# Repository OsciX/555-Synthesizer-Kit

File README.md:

These works were designed by Ryan Davis in 2015, and are licensed under a Creative Commons Attribution-ShareAlike 4.0 International License, which can be found 
at http://creativecommons.org/licenses/by-sa/4.0/ .

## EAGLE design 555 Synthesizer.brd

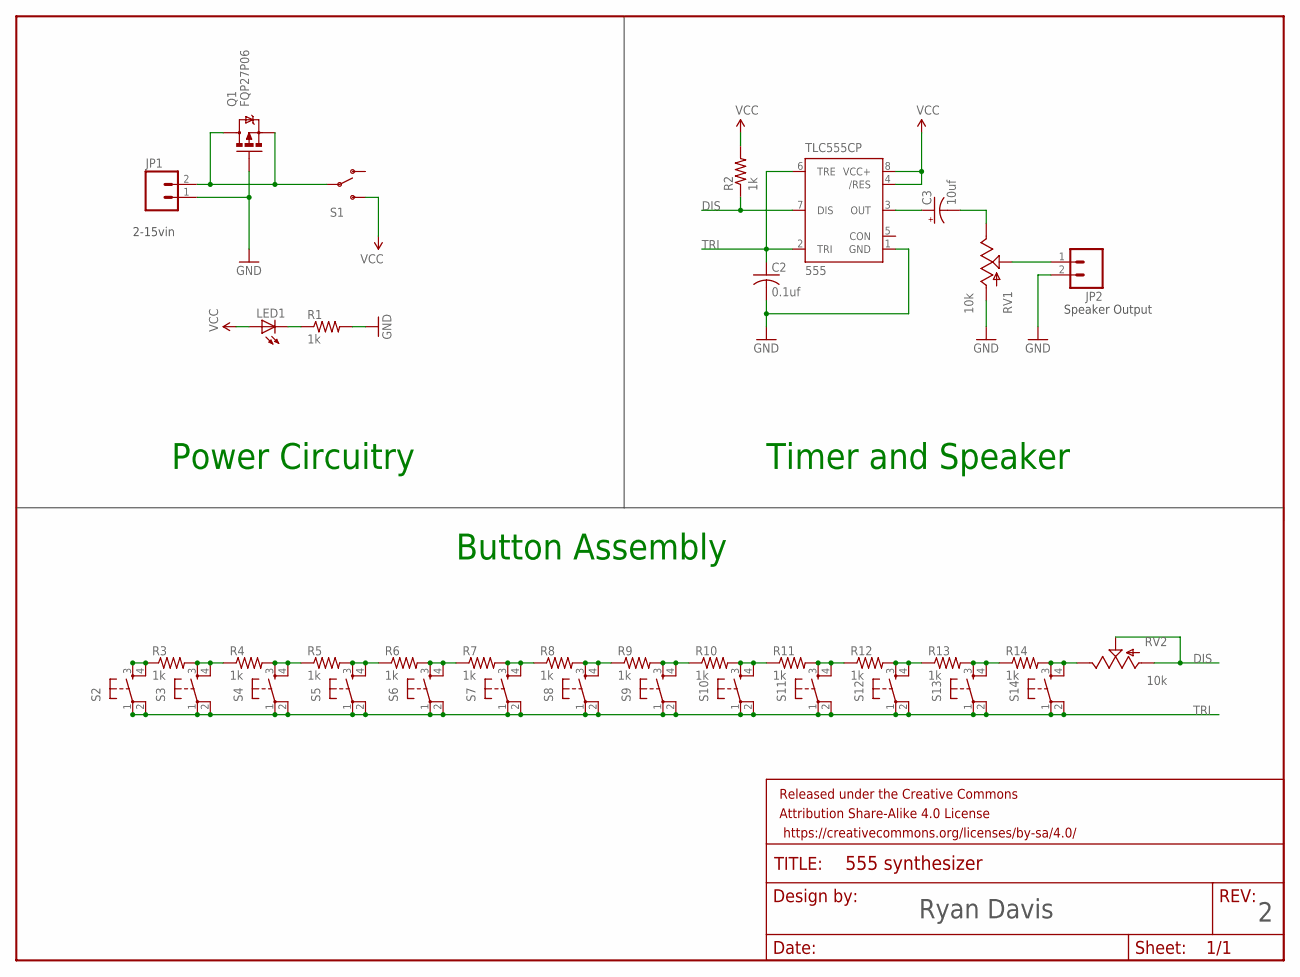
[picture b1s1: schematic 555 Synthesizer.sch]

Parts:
C2: 0.1uf; C025-025X050
C3: 10uf; E2,5-6E
FRAME1: FRAME-LETTERNO_PACKAGE; DUMMY
JP1, JP2: M023.5MM; SCREWTERMINAL-3.5MM-2
LED1: LED5MM
Q1: FQP27P06; TO220V
R1, R2, R3, R4, R5, R6, R7, R8, R9, R10, R11, R12, R13, R14: 1k; 0204/7
RV1, RV2: 10k; ALPS_POT_KIT
S1: SWITCH-SPDTKIT; SWITCH-SPDT_KIT
S2, S3, S4, S5, S6, S7, S8, S9, S10, S11, S12, S13, S14: TAC_SWITCHPTH; TACTILE-PTH
TLC555CP: 555; DIP08-KIT

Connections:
DIS: R2.1, RV2.P$2 (S), RV2.P$3 (A), TLC555CP.7 (DIS)
GND: C2.2, JP1.1, JP2.2, Q1.1 (G), R1.2, RV1.P$3 (A), TLC555CP.1 (GND)
unnamed: JP1.2, Q1.2 (D), Q1.3 (S), S1.2
unnamed: LED1.K (C), R1.1
unnamed: C3.+, TLC555CP.3 (OUT)
unnamed: C3.-, RV1.P$1 (E)
unnamed: JP2.1, RV1.P$2 (S)
unnamed: R3.1, S2.3, S2.4
unnamed: R3.2, R4.1, S3.3, S3.4
unnamed: R4.2, R5.1, S4.3, S4.4
unnamed: R5.2, R6.1, S5.3, S5.4
unnamed: R6.2, R7.1, S6.3, S6.4
unnamed: R7.2, R8.1, S7.3, S7.4
unnamed: R8.2, R9.1, S8.3, S8.4
unnamed: R9.2, R10.1, S9.3, S9.4
unnamed: R10.2, R11.1, S10.3, S10.4
unnamed: R11.2, R12.1, S11.3, S11.4
unnamed: R12.2, R13.1, S12.3, S12.4
unnamed: R13.2, R14.1, S13.3, S13.4
unnamed: R14.2, RV2.P$1 (E), S14.3, S14.4
TRI: C2.1, S2.1, S2.2, S3.1, S3.2, S4.1, S4.2, S5.1, S5.2, S6.1, S6.2, S7.1, S7.2, S8.1, S8.2, S9.1, S9.2, S10.1, S10.2, S11.1, S11.2, S12.1, S12.2, S13.1, S13.2, S14.1, S14.2, TLC555CP.2 (TRI), TLC555CP.6 (TRE)
VCC: LED1.A, R2.2, S1.3 (S), TLC555CP.4 (/RES), TLC555CP.8 (VCC+)

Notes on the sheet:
Power Circuitry
Timer and Speaker
Button Assembly
Ryan Davis
2-15vin
Speaker Output

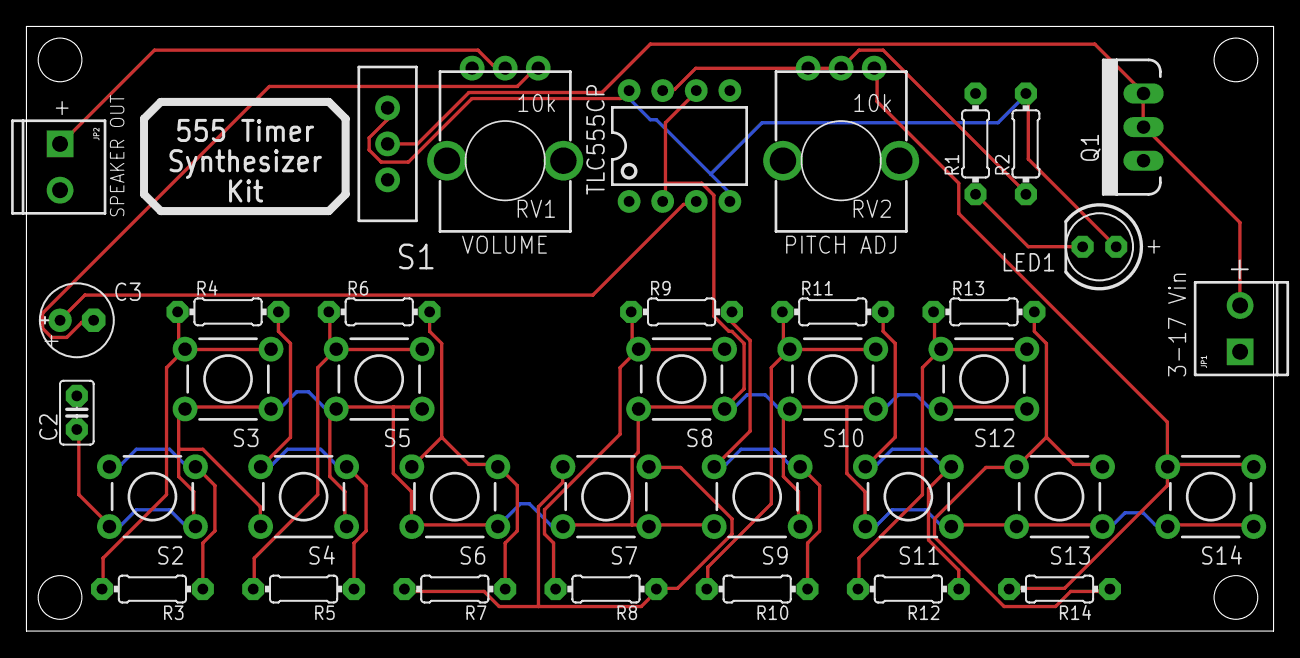
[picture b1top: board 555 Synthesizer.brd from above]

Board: 2 copper layers, 94.3 x 45.7 mm, 42 parts (0 on the bottom side), 22 nets.

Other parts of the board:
U$1, U$2, U$3, U$4: STAND-OFF

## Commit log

2015-07-08 Create 555 Piano.brd
    first commit
2015-08-06 New update!
2015-09-06 Added CMOS 555

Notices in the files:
555 Synthesizer.brd:
Released under the CC BY-SA 4.0 License
http://www.creativecommons.org/licenses/by-sa/4.0
parts and their libraries:
SparkFun-AnalogIC: Licensing:Creative Commons ShareAlike 4.0 International - https://creativecommons.org/licenses/by-sa/4.0
SparkFun-Aesthetics: Released under the Creative Commons Attribution Share-Alike 4.0 License
SparkFun-Aesthetics: https://creativecommons.org/licenses/by-sa/4.0
